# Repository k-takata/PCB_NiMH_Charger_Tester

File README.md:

# NiMH充電器&測定器 (NiMH Charger & Tester) (Rev. 2)

## 概要

ニッケル水素電池を充電したり、内部抵抗や容量を測定します。

参考文献\[1\]や\[2\]の記事を参考に設計した回路となっています。

## 使用したソフトウェア

KiCad 9.0

## 回路図

Rev. 1

## 基板パターン図

Rev. 1

## 部品表

| Reference                 |個数|値    | 説明 |
|---------------------------|----|------|------|
|BT1                        |   1|      |[単3電池ボックス](https://akizukidenshi.com/catalog/g/g100308/)|
|BT2                        |   1|      |[単4電池ボックス](https://akizukidenshi.com/catalog/g/g102670/)|
|C1, C5, C6, C7, C8, C9, C10|   7|0.1μF|[積層セラミックコンデンサー 2.5mm](https://akizukidenshi.com/catalog/g/g113582/)|
|C2                         |   1|100μF|電解コンデンサー φ6.3|
|C3 (\*1)                   |   1| 10μF|積層セラミックコンデンサー 3225M|
|C4 (\*1)                   |   1| 10μF|[積層セラミックコンデンサー 5mm](https://akizukidenshi.com/catalog/g/g103095/)|
|D1, D2                     |   2|1S2076A|小信号用汎用ダイオード|
|D3                         |   1|[OS5REA51A5A](https://akizukidenshi.com/catalog/g/g114209/)|赤色LED (ミルキーレンズ)、充電表示LED|
|D4                         |   1|[OSG5DA51A5A](https://akizukidenshi.com/catalog/g/g114207/)|緑色LED (ミルキーレンズ)、放電表示LED|
|D5 (\*2)                   |   1|[TS260S](https://akizukidenshi.com/catalog/g/g115166/)|表面実装用ショットキーバリアダイオードブリッジ 60V 2A|
|~~D6~~ (\*2)                   |   ~~1~~|~~S1ZB20~~|~~ダイオードブリッジ 200V 0.8A~~|
|F1 (\*3)                   |   1|  0.5A|[ポリヒューズ](https://akizukidenshi.com/catalog/g/g115300/)、表面実装|
|F2 (\*3)                   |   1|  1.1A|[ポリヒューズ](https://akizukidenshi.com/catalog/g/g100507/)|
|J1 (\*4)                   |   1|      |[USB Type-Cコネクター 電源供給用](https://akizukidenshi.com/catalog/g/g116438/)|
|J2 (\*4)                   |   1|      |[USB Type-Cコネクター](https://akizukidenshi.com/catalog/g/g114356/)|
|J3 (\*5)                   |   1|      |ピンヘッダー 1x4、UPDI用|
|J4                         |   1|      |[ロープロファイルピンソケット](https://akizukidenshi.com/catalog/g/g100661/) 1x4、OLED接続用|
|J5                         |   1|      |ピンヘッダー 1x6、シリアル通信用|
|Q1                         |   1|[DTC114EL](https://akizukidenshi.com/catalog/g/g112467/)|抵抗入りNPNトランジスター|
|Q2                         |   1|[DTA114EL](https://akizukidenshi.com/catalog/g/g112464/)|抵抗入りPNPトランジスター|
|Q3                         |   1|[MTB060P06I3](https://akizukidenshi.com/catalog/g/g116095/)|PchパワーMOSFET 60V 16.7A|
|Q4                         |   1|[MTA100N10KRI3](https://akizukidenshi.com/catalog/g/g115847/)|NchパワーMOSFET 100V 10A|
|R1, R2                     |   2|5.1kΩ|緑茶赤金、1/6Wサイズ|
|R3, R4, R12, R15, R16, R19 |   6| 10kΩ|茶黒橙金、1/4Wサイズ|
|R5, R6, R7, R10, R11       |   5|  1kΩ|茶黒赤金、1/4Wサイズ|
|R8 (\*6)                   |   1| 22kΩ|赤赤橙金、1/4Wサイズ、充電表示LED電流制限用 (4.7kΩ～47kΩ)|
|R9 (\*6)                   |   1| 47kΩ|黄紫橙金、1/4Wサイズ、放電表示LED電流制限用 (4.7kΩ～47kΩ)|
|R13, R14                   |   2| 100Ω|茶黒茶金、1/4Wサイズ|
|R17                        |   1|  10Ω|茶黒黒金茶、[酸化金属皮膜抵抗 3W 10Ω](https://akizukidenshi.com/catalog/g/g111015/)|
|R18                        |   1|   1Ω|茶黒黒銀茶、[酸化金属皮膜抵抗 3W 1Ω](https://akizukidenshi.com/catalog/g/g111013/)|
|SW1                        |   1|[DTS-63-N-V-RED](https://akizukidenshi.com/catalog/g/g103646/)|タクトスイッチ (赤色)|
|SW2                        |   1|[DTS-63-N-V-GRN](https://akizukidenshi.com/catalog/g/g103651/)|タクトスイッチ (緑色)|
|SW3                        |   1|[DTS-63-N-V-BLU](https://akizukidenshi.com/catalog/g/g103649/)|タクトスイッチ (水色)|
|U1                         |   1|[AVR64DD28-I/SP](https://akizukidenshi.com/catalog/g/g118314/)|AVRマイコン|
|U2                         |   1|[NJU7043](https://akizukidenshi.com/catalog/g/g106840/)|2回路入入出力フルスイングオペアンプ|
|U3, U5                     |   1|[MCP9700BT-E/TT](https://akizukidenshi.com/catalog/g/g130948/)|温度センサーIC|
|U4                         |   1|[TL431](https://akizukidenshi.com/catalog/g/g112018/)|シャントレギュレーター 2.495V|

注:
* (\*1) C3, C4はどちらかを選択します。基板上にはC3の表示のみあります。
* (\*2) ~~(Rev. 2から) D5, D6はどちらかを選択します。基板上にはD6の表示のみあります。~~ D6はピンピッチが間違っていたため取り付け不可。
* (\*3) F1, F2はどちらかを選択します。基板上にはF1の表示のみあります。
* (\*4) J1, J2は部品の入手状況や実装難易度を考慮してどちらかを選択します。J1を選択した場合は、基板から少しはみ出す状態で取り付けることになります。J2を選択した場合は、J1用のランドとコネクター本体がショートしないようにポリイミドテープ等で絶縁する必要があります。
* (\*5) Rev. 1ではピンソケット 1x3でしたが、Rev. 2ではピンヘッダー 1x4に変更されています。
* (\*6) LEDの明るさを変えたい場合は適宜値を変更します。ここでは暗めに設定しています。

## 作成

[NiMH充電器&測定器の作成 (その1、ハードウェア編)](https://zenn.dev/k_takata/articles/nimh-charger-tester-1)を参照してください。

## 使用方法

[NiMH充電器&測定器の作成 (その2、ソフトウェア編)](https://zenn.dev/k_takata/articles/nimh-charger-tester-2)を参照してください。

## 変更差分

Rev. 2での変更点は以下の通りです。

* 充放電電流を測定できるようにTP2 (Vchg)とPF0ピンを接続し、TP3 (Vdis)とPF1ピンを接続。
* ICを取り外しやすくなるようにAVRマイコンの位置を調整。
* UPDIコネクターを[AVR Programming Adapter](https://www.microchip.com/en-us/development-tool/AC31S18A)に合わせて、4pinのピンヘッダーに変更。向きも反転。
* OLEDのコネクターの位置を調整。
* ピンヘッダーやピンソケットのぐらつきが少なくなるようにドリル径を調整。
* 単3電池の "+" マークのシルクの位置がずれていたのを修正。
* ブリッジダイオードをD5とD6で選択可能にした。
* TTLシリアル端子のピン順序(シルク)が逆になっていたのを修正。

## 完成品

充電完了後にグラフを表示している様子 (Rev. 1):

## 参考文献

1. [トランジスタ技術SPECIAL No.135 Liイオン/鉛/NiMH蓄電池の充電&電源技術](https://shop.cqpub.co.jp/hanbai/books/46/46751.html)<br/>
   「第4章　研究！ ニッケル水素蓄電池の耐久テスト」 下間 憲行著
2. [トランジスタ技術SPECIAL No.170 教科書付き 小型バッテリ電源回路](https://www.cqpub.co.jp/trs/trsp170.htm)<br/>
   「Appendix 1　充放電回数の限界…サイクル耐久特性の実測」 下間 憲行著
3. [電池応用ハンドブック](https://www.cqpub.co.jp/hanbai/books/34/34461.htm)

## License

CC0

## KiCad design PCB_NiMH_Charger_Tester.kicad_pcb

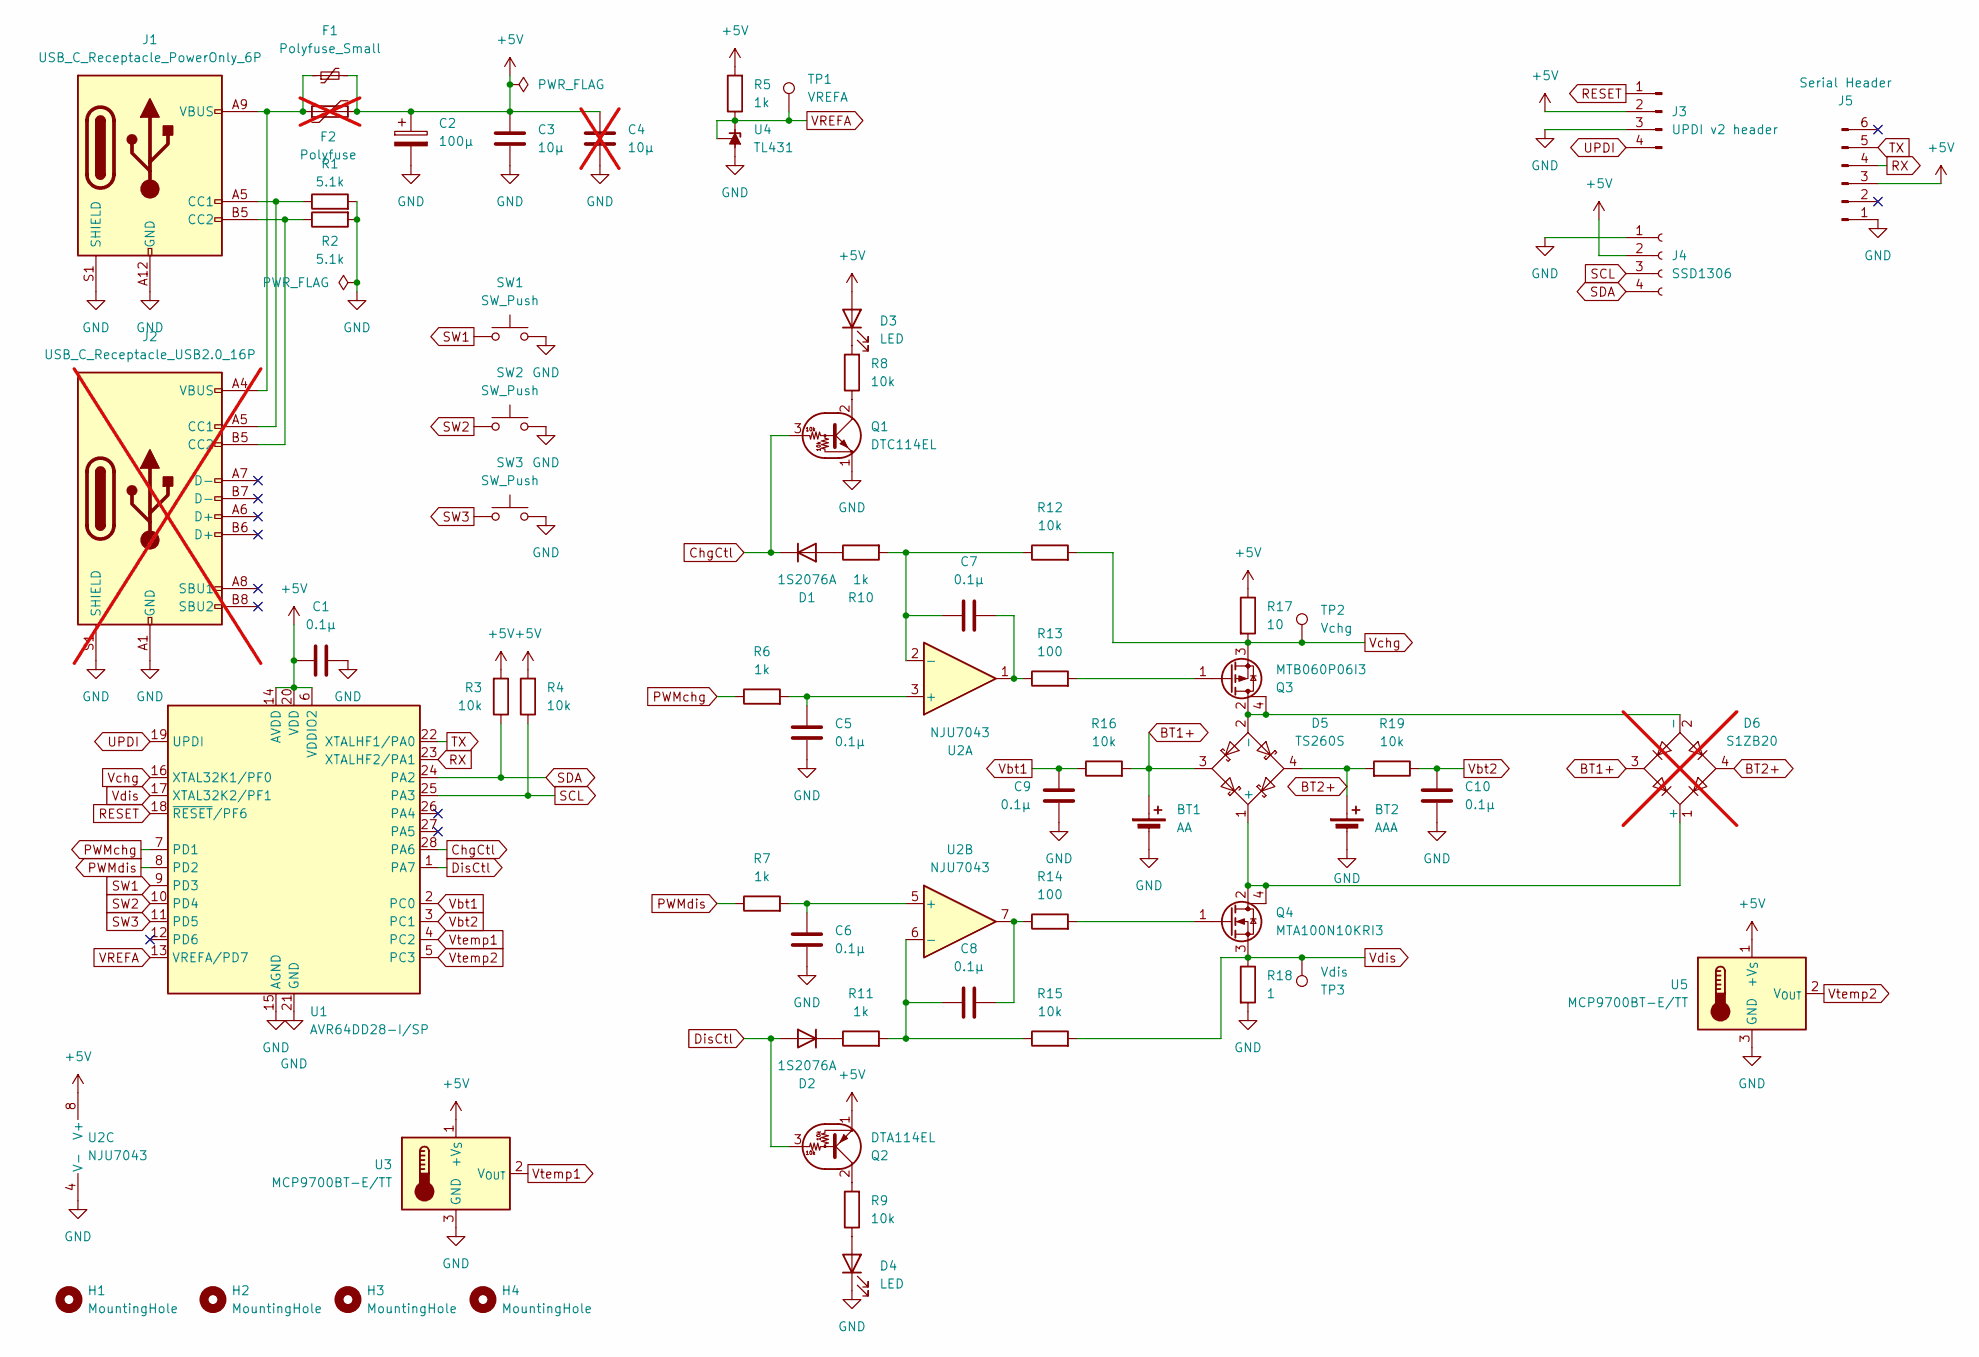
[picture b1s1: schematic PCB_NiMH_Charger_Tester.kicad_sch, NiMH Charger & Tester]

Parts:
BT1: AA; BatteryHolder_Keystone_2460_1xAA
BT2: AAA; BatteryHolder_Keystone_2466_1xAAA
C1, C5, C6, C7, C8, C9, C10: 0.1μ; C_Disc_D3.0mm_W1.6mm_P2.50mm
C2: 100μ; CP_Radial_D6.3mm_P2.50mm
C3: 10μ; C_1210_3225Metric_Pad1.33x2.70mm_HandSolder
C4: 10μ; C_Disc_D4.7mm_W2.5mm_P5.00mm; not fitted
D1, D2: 1S2076A; D_DO-35_SOD27_P7.62mm_Horizontal
D3: LED; LED_D5.0mm
D4: LED; LED_D5.0mm_Clear
D5: TS260S; TSSOP-4_4.4x5mm_P4mm
D6: S1ZB20; Diode_Bridge_DIP-4_W5.08mm_P2.54mm; not fitted
F1: Polyfuse_Small; Fuse_1206_3216Metric_Pad1.42x1.75mm_HandSolder
F2: Polyfuse; C_Disc_D4.3mm_W1.9mm_P5.00mm; not fitted
H1, H2, H3, H4: MountingHole; MountingHole_3.2mm_M3
J1: USB_C_Receptacle_PowerOnly_6P; USB_C_Receptacle_GCT_USB4125-xx-x_6P_TopMnt_Horizontal
J2: USB_C_Receptacle_USB2.0_16P; USB_C_Receptacle_GCT_USB4105-xx-A_16P_TopMnt_Horizontal; not fitted
J3: UPDI v2 header; PinHeader_1x04_P2.54mm_Vertical
J4: SSD1306; PinSocket_1x04_P2.54mm_Vertical
J5: Serial Header; PinHeader_1x06_P2.54mm_Vertical
Q1: DTC114EL; TO-92_Inline_Wide
Q2: DTA114EL; TO-92_Inline_Wide
Q3: MTB060P06I3; TO-251-3-1EP_Horizontal_TabDown
Q4: MTA100N10KRI3; TO-251-3-1EP_Horizontal_TabDown
R1, R2: 5.1k; R_Axial_DIN0204_L3.6mm_D1.6mm_P5.08mm_Horizontal
R3, R4, R8, R9: 10k; R_Axial_DIN0207_L6.3mm_D2.5mm_P7.62mm_Horizontal
R5, R6, R7, R10, R11: 1k; R_Axial_DIN0207_L6.3mm_D2.5mm_P2.54mm_Vertical
R12, R15, R16, R19: 10k; R_Axial_DIN0207_L6.3mm_D2.5mm_P2.54mm_Vertical
R13, R14: 100; R_Axial_DIN0207_L6.3mm_D2.5mm_P2.54mm_Vertical
R17: 10; R_Axial_DIN0614_L14.3mm_D5.7mm_P20.32mm_Horizontal
R18: 1; R_Axial_DIN0614_L14.3mm_D5.7mm_P20.32mm_Horizontal
SW1, SW2, SW3: SW_Push; SW_PUSH_6mm
TP1: VREFA; TestPoint_THTPad_D1.5mm_Drill0.7mm
TP2: Vchg; TestPoint_THTPad_D1.5mm_Drill0.7mm
TP3: Vdis; TestPoint_THTPad_D1.5mm_Drill0.7mm
U1: AVR64DD28-I/SP; DIP-28_W7.62mm
U2: NJU7043; DIP-8_W7.62mm
U3, U5: MCP9700BT-E/TT; SOT-23_Handsoldering
U4: TL431; TO-92_Inline_Wide

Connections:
+5V: C1.2, C2.1, C3.1, C4.1, D3.2 (A), F1.2, F2.2, J3.2, J4.2, J5.3, Q2.1 (G), R3.2, R4.2, R5.2, R17.1, U1.6 (VDDIO2), U1.14 (AVDD), U1.20 (VDD), U2.8 (V+), U3.1 (+V_{S}), U5.1 (+V_{S})
BT1+: BT1.1 (+), D5.3, D6.3, R16.2
BT2+: BT2.1 (+), D5.4, D6.4, R19.2
ChgCtl: D1.1 (K), Q1.3 (I), U1.28 (PA6)
DisCtl: D2.2 (A), Q2.3 (I), U1.1 (PA7)
GND: BT1.2 (-), BT2.2 (-), C1.1, C2.2, C3.2, C4.2, C5.1, C6.1, C9.1, C10.1, D4.1 (K), J1.A12 (GND), J1.B12 (GND), J1.S1 (SHIELD), J2.A1 (GND), J2.A12 (GND), J2.B1 (GND), J2.B12 (GND), J2.S1 (SHIELD), J3.3, J4.1, J5.1, Q1.1 (G), R1.2, R2.2, R18.2, SW1.2, SW2.2, SW3.2, U1.15 (AGND), U1.21 (GND), U2.4 (V-), U3.3 (GND), U4.2 (A), U5.3 (GND)
unnamed: C7.2, R13.1, U2.1
unnamed: C8.2, R14.1, U2.7
unnamed: D1.2 (A), R10.1
unnamed: D2.1 (K), R11.1
unnamed: D3.1 (K), R8.2
unnamed: D4.2 (A), R9.1
unnamed: D5.1 (+), D6.1 (+), Q4.2 (D), Q4.4 (D)
unnamed: D5.2 (-), D6.2 (-), Q3.2 (D), Q3.4 (D)
unnamed: F1.1, F2.1, J1.A9 (VBUS), J1.B9 (VBUS), J2.A4 (VBUS), J2.A9 (VBUS), J2.B4 (VBUS), J2.B9 (VBUS)
unnamed: J1.A5 (CC1), J2.A5 (CC1), R1.1
unnamed: J1.B5 (CC2), J2.B5 (CC2), R2.1
unnamed: Q1.2 (O), R8.1
unnamed: Q2.2 (O), R9.2
unnamed: Q3.1 (G), R13.2
unnamed: Q4.1 (G), R14.2
unnamed: C5.2, R6.2, U2.3 (+)
unnamed: C7.1, R10.2, R12.1, U2.2 (-)
unnamed: C6.2, R7.2, U2.5 (+)
unnamed: C8.1, R11.2, R15.1, U2.6 (-)
PWMchg: R6.1, U1.7 (PD1)
PWMdis: R7.1, U1.8 (PD2)
RESET: J3.1, U1.18 (~RESET/PF6)
RX: J5.4, U1.23 (XTALHF2/PA1)
SCL: J4.3, R4.1, U1.25 (PA3)
SDA: J4.4, R3.1, U1.24 (PA2)
SW1: SW1.1, U1.9 (PD3)
SW2: SW2.1, U1.10 (PD4)
SW3: SW3.1, U1.11 (PD5)
TX: J5.5, U1.22 (XTALHF1/PA0)
UPDI: J3.4, U1.19 (UPDI)
VREFA: R5.1, TP1.1, U1.13 (VREFA/PD7), U4.1 (REF), U4.3 (K)
Vbt1: C9.2, R16.1, U1.2 (PC0)
Vbt2: C10.2, R19.1, U1.3 (PC1)
Vchg: Q3.3 (S), R12.2, R17.2, TP2.1, U1.16 (XTAL32K1/PF0)
Vdis: Q4.3 (S), R15.2, R18.1, TP3.1, U1.17 (XTAL32K2/PF1)
Vtemp1: U1.4 (PC2), U3.2 (V_{OUT})
Vtemp2: U1.5 (PC3), U5.2 (V_{OUT})

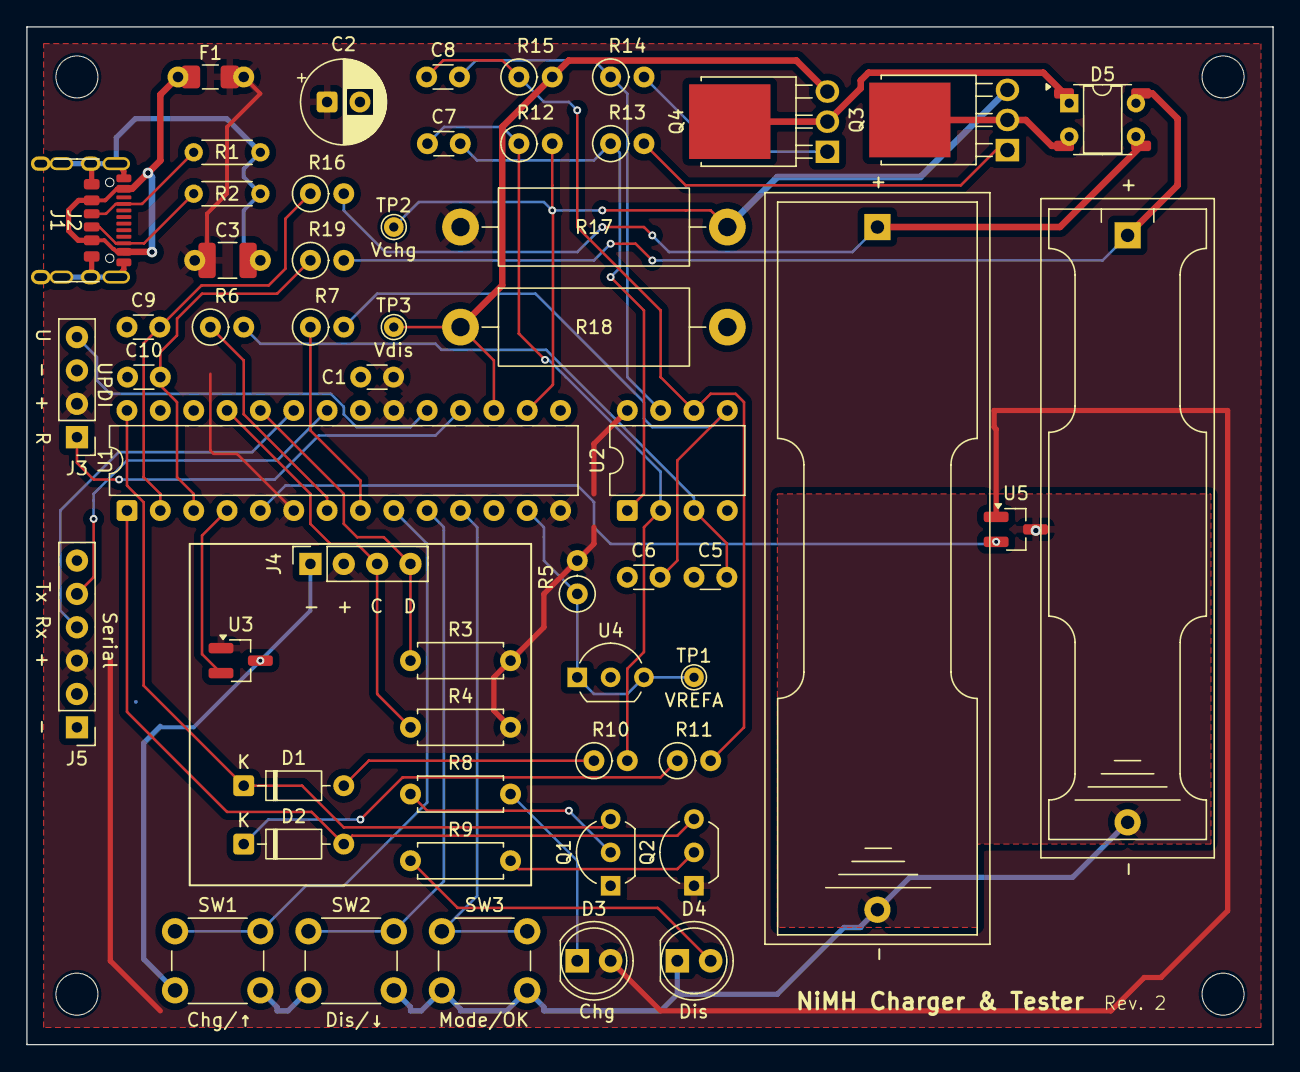
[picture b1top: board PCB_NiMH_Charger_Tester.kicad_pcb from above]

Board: 2 copper layers, 94.9 x 77.5 mm, 63 parts (0 on the bottom side), 43 nets.

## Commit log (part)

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2025-08-12 Initial implementation
2025-08-13 Add title
2025-08-14 Update project settings
2025-08-14 Fix parts name
2025-08-14 Add README
2025-08-18 シルクの位置を調整
    BT1の "+" の位置がずれていたのを修正。
2025-08-24 Update
    * Adjust the position of SS1306.
    * Support S1ZB20.
2025-08-24 Rev. 2
2025-08-30 Adjust OLED hole size
2025-08-31 Adjust drill size
2025-08-31 Adjust U1 position
2025-08-31 Update UPDI connector
    Use the official UPDI v2 connector.
    See "AVR Programming Adapter":
    https://www.microchip.com/en-us/development-tool/AC31S18A
2025-08-31 W/A for DRC errors
    * Adjust +5V zones. Explicitly connect two zones.
    * Adjust D5 silkscreen.
2025-08-31 Adjust J3,J5 position
2025-09-04 Adjust resistor values
2025-09-04 Add color codes
2025-09-04 Replace S1ZB20 symbol
    It is not a Schottky Bridge, PN Bridge.
2025-09-05 Reverse Serial Header
2025-09-11 Change drill size
    J3, J5: Normal pin header: 0.9mm -> 0.8mm
    J4: Pin socket: 0.9mm -> 0.8mm
2025-09-18 Revise README with project link and completion status
2025-09-19 Update silk
2025-09-25 Connect Vchg/Vdis to AVR
    Also, change J3/J5 direction.
2025-09-30 Update button name
2025-09-30 Fabrication
2025-10-12 Add photo and link
2025-10-15 Revert resistor values
2025-10-15 Update README for Rev. 2
2025-10-15 Update README
    Change the color of the switches.
2025-10-17 Change resistor values
2025-10-18 Stop using D6
    Footprint was wrong.
2025-11-14 Fix D6 footprint
